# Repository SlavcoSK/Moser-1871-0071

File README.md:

# Moser ChromStyle Pro 1871 – rekonštrukcia PCB a schémy

Reverzné inžinierstvo dosky strihacieho strojčeka **Moser/Wahl 1871-7176**, PCB **E190688**, s mikrokontrolérom **ATtiny461V-10SU**.

## Aktuálne súbory

- [Moser_1871_FINAL_3D_SYNC1.kicad_pcb](Moser_1871_FINAL_3D_SYNC1.kicad_pcb) – aktuálna ručne rekonštruovaná PCB; hlavný zdroj pravdy projektu.
- [Moser_1871_FINAL_3D_SYNC1.kicad_sch](Moser_1871_FINAL_3D_SYNC1.kicad_sch) – schéma odvodená z PCB.

PCB a schéma majú rovnaký základ názvu, aby ich bolo možné zaradiť do jedného projektu KiCad 9. Lokálny projektový súbor `.kicad_pro` je možné vytvoriť alebo ponechať v rovnakom priečinku.

## 3D náhľad dosky

### Predná strana – F.Cu

### Zadná strana – B.Cu

## Zásadné pravidlo rekonštrukcie

Pri rozpore platí toto poradie dôveryhodnosti:

1. meranie a sledovanie spojov na originálnej PCB,
2. čitateľná fotografia originálnej dosky,
3. aktuálny ručne opravený PCB súbor,
4. datasheet jednoznačne identifikovanej súčiastky,
5. staré automatické siete, staré schémy a odhady podľa markingu.

Geometria používateľovej PCB je nadradená. Cesty, zóny, polohy, orientácie ani číslovanie plôšok sa nemajú automaticky meniť. Schéma je rekonštrukcia z PCB, nie autorita nad originálnou doskou.

## Potvrdené tranzistory

| Marking | Typ | Tranzistory | Pinout |
|---|---|---|---|
| FZT968 | FZT968 PNP, SOT-223 | T1, T2 | 1=B, 2=C/tab, 3=E |
| 6CW | BC817-40 NPN, SOT-23 | T4, T5, T6, T13, T15 | 1=B, 2=E, 3=C |
| 1K / 1.K | BC848B NPN, SOT-23 | T3, T11 | 1=B, 2=E, 3=C |
| 3.B | BC856B PNP, SOT-23 | T8, T9, T12, T14 | 1=B, 2=E, 3=C |

Tieto identifikácie sú v KiCad súboroch označené ako **POTVRDENÉ – NEMENIŤ**.

### T7

- marking **HDY0**,
- digitálny tranzistor/BRT potvrdený,
- presný katalógový typ a vnútorné rezistory zatiaľ nepotvrdené,
- aktuálne PCB: T7.1 = N012, T7.2 = GND, T7.3 = N010.

### T10

- marking **P8W** a zvislé číslo **67**,
- digitálny tranzistor/BRT potvrdený,
- presný katalógový typ a vnútorné rezistory zatiaľ nepotvrdené,
- T10.1 = Adapter+,
- T10.2 = BAT+,
- T10.3 = R16.2.

Staré identifikácie T10 ako PMBZ5246B a definitívne tvrdenie PDTC143ET sa nepovažujú za potvrdené.

## Diódy a indikácia

### D1 – ochrana motora

- marking **S4**,
- vpravo je anóda,
- vľavo je katóda,
- aktuálne číslovanie: 1=A, 2=K,
- funkcia ochrannej/flyback diódy motora je potvrdená,
- presný katalógový typ zostáva otvorený; SS24-class je iba pracovný kandidát.

### LED stavu batérie

- D3, D4 a D5 sú zelené LED indikácie nabitia,
- D6 je červená LED nízkeho/vybitého stavu,
- pin 1 = anóda, pin 2 = katóda,
- LED sú ovládané cez katódové vetvy.

Potvrdené väzby:

- D3.2 → R26.1; R26.2 → U1.12,
- D4.2 → R27.1; R27.2 → U1.3,
- D5.2 → R31.2; R31.1 → U1.8,
- D6.2 → R34.1 → R32.1; R32.2 → T14.1.

## Potvrdené merania

- motor: približne **530 mA pri 4 V**,
- akumulátor: **3,6 V / 2000 mAh**, externý test približne **1700 mAh a 6,2 Wh pri 300 mA**,
- automatické vypnutie motora nastalo približne pri **2,885–2,888 V**,
- R37–R40: marking R100, hodnota **0,100 Ω**,
- R41: **0,30 Ω**,
- JP1 a JP2: nulové MELF prepojky, DCR približne **6 mΩ**, indukčnosť pod **0,1 µH**.

## Podpora projektu

Ak vám táto rekonštrukcia pomohla alebo ste jej podklady použili, budeme radi, ak projektu udelíte aspoň **⭐ hviezdičku na GitHube**. Je to jednoduchý spôsob, ako oceniť čas, merania na originálnej PCB a našu spoločnú prácu vloženú do rekonštrukcie.

## Aktuálna pracovná etapa

Dopĺňajú sa kontrolné plôšky **TP**. Každý TP sa najprv vytvorí a pripojí v schéme, následne sa cez aktualizáciu zo schémy prenesie do PCB a umiestni na fyzickú kontrolnú plôšku alebo koniec príslušného prekovu.

Projekt je stále pracovná rekonštrukcia a zatiaľ nie je určený ako výrobný podklad.

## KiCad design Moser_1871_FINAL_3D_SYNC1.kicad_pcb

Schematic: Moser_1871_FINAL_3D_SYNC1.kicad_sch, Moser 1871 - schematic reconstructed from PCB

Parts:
C1, C4: 100 nF (meas. 98 nF)
C2: 100 nF (meas. 97 nF)
C3: 1 nF
C5: 100 nF (meas. 96 nF)
C6: 1 µF (meas. ~0.9 µF)
C8, C10: C1 micro F
C9: C96nF
C11: C97nF
C12: C101nF
D1: S4; ochranna dioda motora; 1=A vpravo, 2=K vlavo;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
D2: Si signal diode; Vf=0.585 V; 1=K, 2=A
D3, D4, D5: ZELENA LED; 1=A, 2=K; riadenie katodou
D6: CERVENA LED LOW BAT; 1=A, 2=K; riadenie katodou
D7: D Si signal diode; Vf=0.585 V; 1=K, 2=A
D10: D
JP1, JP2: 0 ohm MELF; DCR priblizne 6 mOhm; L pod 0.1 uH; P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
P_ADAPTER_NEG1: ADAPTER - independent
P_ADAPTER_POS1: Adapter +
P_BAT_NEG1: BATTERY - independent
P_BAT_POS1: BATTERY + independent
P_MOTOR_NEG1: MOTOR - independent
P_MOTOR_POS1: MOTOR + independent
R1, R10: 10 kΩ
R2: 560 Ω
R3: 33 Ω
R4, R12, R13: 100 Ω
R5: 150 Ω
R6, R7, R8: 1 kΩ
R9: 10 kΩ (measured)
R11: 100 kΩ
R14, R24, R28: R1001
R15, R18, R19, R23, R32, R36: R103
R16, R37, R38, R39, R40: R100
R17: R5603
R20, R21: R5602
R22: R2203
R25: R222
R26, R27, R31, R34: R151
R29: R472
R30: R183
R33: R331
R35: R104
R41: 0.30 ohm; POTVRDENE
SPK1: SPEAKER 3D (existing solder vias retained)
T1, T2: FZT968 PNP; 1=B, 2=C/tab, 3=E; POTVRDENE
T3: BC848B NPN; marking 1K; 1=B, 2=E, 3=C; POTVRDENE
T4, T5, T6, T13, T15: BC817-40 NPN; marking 6CW; 1=B, 2=E, 3=C; POTVRDE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
T7: HDY0; DIGITALNY TRANZISTOR POTVRDENY; PRESNY TYP 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
T8, T9, T12, T14: BC856B PNP; marking 3.B; 1=B, 2=E, 3=C; POTVRDENE
T10: P8W + zvisle 67; DIGITALNY TRANZISTOR POTVRDENY; 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
T11: BC848B NPN; marking 1.K; 1=B, 2=E, 3=C; POTVRDENE
TP1: PCB PAD at 192.000,64.500; original unnumbered
TP2: PCB PAD at 177.500,93.500; original unnumbered
TP3: PCB PAD at 175.500,117.750; original A-
TP4: PCB PAD at 178.500,47.750; original unnumbered
TP5: PCB PAD at 194.500,117.750; original +A
TP6: PCB PAD at 178.500,49.500; original unnumbered
TP7: PCB PAD at 179.500,93.500; original unnumbered
TP8: TestPoint; TestPoint_Pad_D1.0mm
TP9: TestPoint
U1: ATtiny461V-10SU SOIC-20; POTVRDENE

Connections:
Adapter+: C11.2, D7.2 (A), P_ADAPTER_POS1.+A (A), R25.2, R30.2, R33.2, T2.3 (E), T10.1, T15.3, TP5.1
Adapter_Sense: D10.2, R33.1, T15.1
BAT+: P_BAT_POS1.+B (B), R22.1, T2.2 (C), T9.2, T10.2, T12.2, TP1.1
GND: C2.1, C3.1, C3.2, C4.2, C5.1, C5.2, C6.1, C6.2, C8.1, C9.2, C10.1, C11.1, C12.1, D10.1, JP1.1, JP2.1, P_ADAPTER_NEG1.-A (A), P_BAT_NEG1.-B (B), R2.1, R2.2, R4.2, R6.2, R9.2, R11.2, R14.1, R20.2, R29.1, R35.1, R39.2, R40.2, R41.2, T3.2 (E), T4.1 (B), T4.2 (E), T5.2 (E), T6.2 (E), T7.2, T11.2, T13.2, TP2.1, U1.6, U1.7, U1.13, U1.15, U1.16, U1.20
Isense: D1.1 (A), JP1.2, JP2.2, R12.1, R31.1, R37.1, R38.1, R39.1, R40.1, U1.8
MOTOR+: D1.2 (K), P_MOTOR_POS1.+M (M), R8.1, T1.2 (C)
N001: R24.2, T13.1
N002: R25.1, T13.3
N003: R17.1, T9.1
N004: R21.1, T9.3
N005: R22.2
N006: D3.1 (A), D4.1 (A), D5.1 (A), D6.1 (A), T12.3, T14.2, T15.2
N007: D5.2 (K), R31.2
N008: C9.1, R18.1, R20.1, R21.2
N009: R18.2, U1.14
N010: C8.2, R16.1, T7.3
N011: R16.2, T10.3
N012: C10.2, R41.1, T7.1, T8.2
N013: D4.2 (K), R27.1
N014: R27.2, U1.3
N015: D7.1 (K), R24.1, R28.1, U1.17
N016: R23.1, R28.2, T12.1
N017: P_MOTOR_NEG1.-M (M), R11.1, R37.2, R38.2
N018: D6.2 (K), R34.1
N019: R32.1, R34.2, T14.3, U1.1
N020: R15.2, R17.2
N021: R14.2
N022: C12.2, R35.2, R36.1
N023: TP4.1
N024: R29.2, R30.1, T3.1 (B)
N025: R19.1, T11.1
N026: R23.2, T11.3
N027: D3.2 (K), R26.1
N028: R26.2, U1.12
N029: R32.2, T14.1
N030: R15.1, T8.1
N031: R1.1, R19.2, T8.3
N032: TP6.1
N033: R13.1, R36.2, U1.18
N034: C2.2, R8.2, TP7.1, U1.9
N035: R13.2, T6.1 (B)
N036: T6.3 (C)
N037: C1.2, D2.1 (K), T3.3 (C)
N038: D2.2 (A), R4.1
N039: R3.1, T4.3 (C)
N040: R3.2, T1.1 (B)
N041: C4.1, R10.2, U1.5
N042: R1.2, R9.1, U1.11
N043: T1.3 (E)
N044: C1.1, R10.1, U1.10
N045: R7.1, U1.2
N046: R6.1, U1.4
N047: R12.2, U1.19
N048: R5.1, T5.3 (C)
N049: R7.2, T5.1 (B)
N050: R5.2, T2.1 (B)
N051: TP3.1

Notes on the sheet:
T7: marking HDY0; exact type unconfirmed. Pin numbering follows the attached PCB revision (5).
SPK1 is 3D-only in the PCB and therefore has no electrical pins in this draft.
T10: pin 1=Adapter+, pin 2=BAT+, pin 3=R16.2 network. Marking P8W + vertical 67; exact type unconfirmed.
MOSER 1871 - COMPLETE CONNECTIVITY DRAFT EXTRACTED FROM PCB
Adapter_Sense is the physical island R33.1-D10.2-T15.1. Verify against the original board before manufacturing.

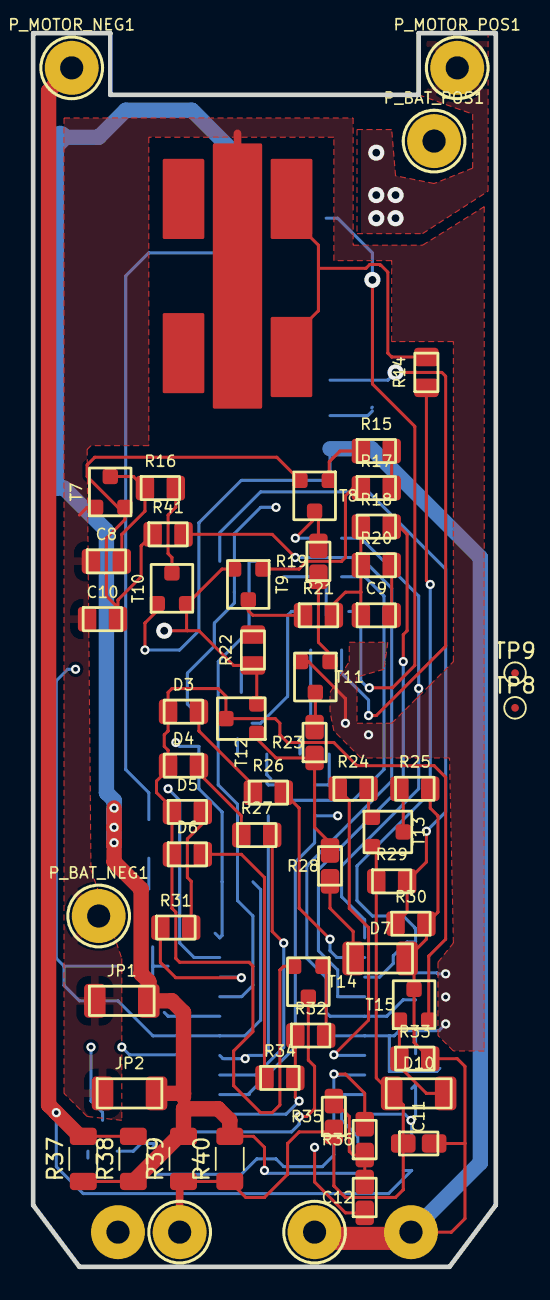
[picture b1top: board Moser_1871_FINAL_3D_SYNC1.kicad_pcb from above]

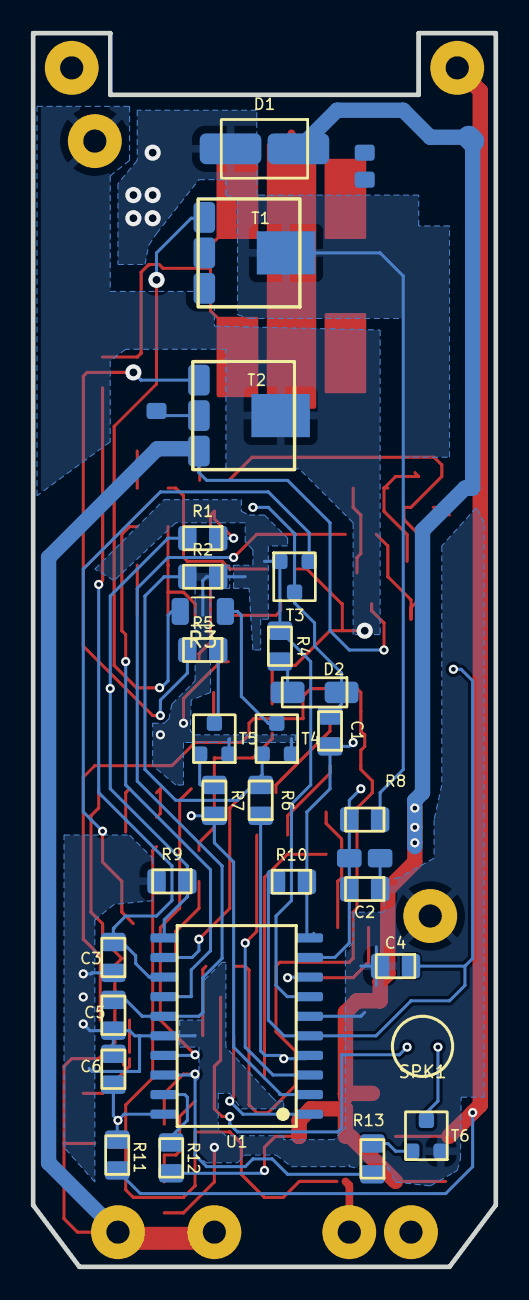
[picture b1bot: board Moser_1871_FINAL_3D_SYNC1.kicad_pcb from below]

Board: 2 copper layers, 30.0 x 80.0 mm, 94 parts (29 on the bottom side), 50 nets.

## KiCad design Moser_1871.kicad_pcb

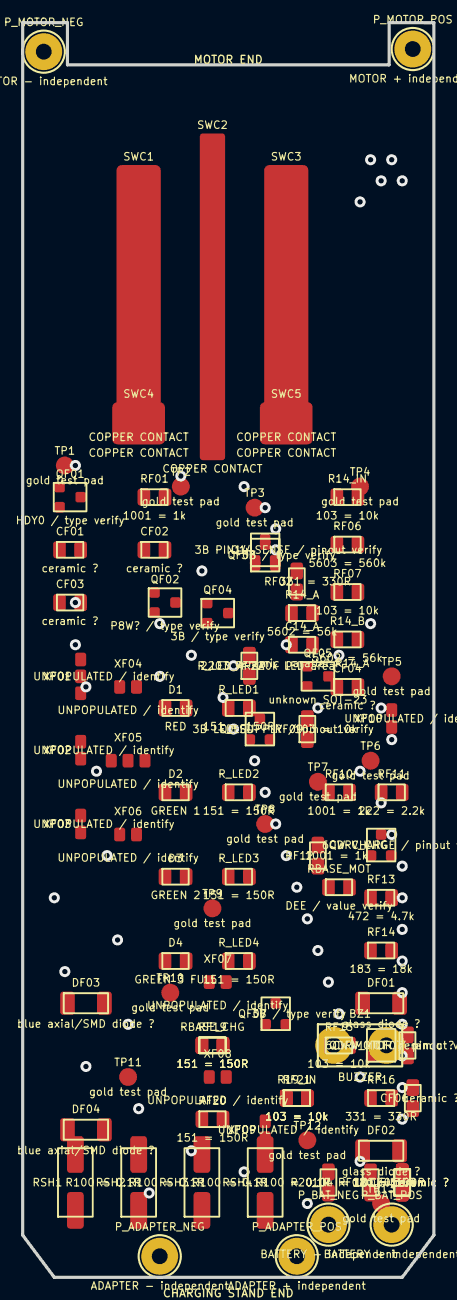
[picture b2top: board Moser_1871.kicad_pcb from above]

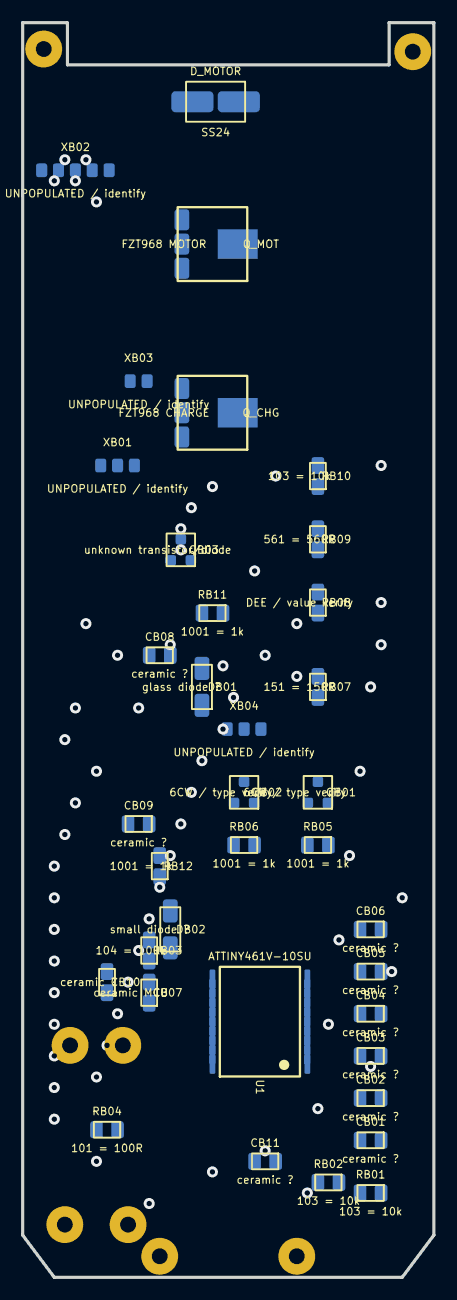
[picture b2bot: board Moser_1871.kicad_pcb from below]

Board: 2 copper layers, 39.0 x 119.0 mm, 130 parts (36 on the bottom side), 20 nets, no tracks yet.

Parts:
BZ1: BUZZER; TH_2P
C14_A: ceramic parallel R14_A; 0805_2P
C20_FILTER: ceramic ?; 0805_2P
CB01, CB02, CB03, CB04, CB05, CB06, CB08, CB09, CB10, CB11: ceramic ?; 0805_2P
CB07: ceramic MCU; 0805_2P
CF01, CF02, CF03, CF04, CF05, CF06, CF07: ceramic ?; 0805_2P
D1: RED; 0805_2P
D2: GREEN 1; 0805_2P
D3: GREEN 2; 0805_2P
D4: GREEN 3 FULL; 0805_2P
DB01: glass diode ?; MELF_2P
DB02: small diode ?; MELF_2P
DF01, DF02: glass diode ?; MELF_2P
DF03, DF04: blue axial/SMD diode ?; MELF_2P
D_MOTOR: SS24; SMB_2P
P_ADAPTER_NEG: ADAPTER - independent; TH_SINGLE_PAD
P_ADAPTER_POS: ADAPTER + independent; TH_SINGLE_PAD
P_BAT_NEG: BATTERY - independent; TH_SINGLE_PAD
P_BAT_POS: BATTERY + independent; TH_SINGLE_PAD
P_MOTOR_NEG: MOTOR - independent; TH_SINGLE_PAD
P_MOTOR_POS: MOTOR + independent; TH_SINGLE_PAD
Q14: 3B PIN14 SENSE / pinout verify; SOT-23
QB01, QB02: 6CW / type verify; SOT-23
QB03: unknown transistor/diode; SOT-23
QDRV_CHG: 6CW CHARGE / pinout verify; SOT-23
QDRV_MOT: 6CW MOTOR / pinout verify; SOT-23
QF01: HDY0 / type verify; SOT-23
QF02: P8W? / type verify; SOT-23
QF03, QF04, QF07: 3B / type verify; SOT-23
QF05: unknown SOT-23; SOT-23
Q_CHG: FZT968 CHARGE; SOT-223
Q_LED: 3B LED SUPPLY / pinout verify; SOT-23
Q_MOT: FZT968 MOTOR; SOT-223
R14_A, R14_B: 5602 = 56k; 0805_2P
R14_IN, R19_IN: 103 = 10k; 0805_2P
R20_IN: 104 = 100k; 0805_2P
RB01, RB02, RB10: 103 = 10k; 0805_2P
RB03: 104 = 100k; 0805_2P
RB04: 101 = 100R; 0805_2P
RB05, RB06, RB11, RB12: 1001 = 1k; 0805_2P
RB07: 151 = 150R; 0805_2P
RB08: DEE / value verify; 0805_2P
RB09: 561 = 560R; 0805_2P
RBASE_CHG: 151 = 150R; 0805_2P
RBASE_MOT: DEE / value verify; 0805_2P
RF01, RF10, RF12: 1001 = 1k; 0805_2P
RF02, RF16: 331 = 330R; 0805_2P
RF06: 5603 = 560k; 0805_2P
RF07, RF09, RF15, RF21: 103 = 10k; 0805_2P
RF11: 222 = 2.2k; 0805_2P
RF13: 472 = 4.7k; 0805_2P
RF14: 183 = 18k; 0805_2P
RF18: 101 = 100R; 0805_2P
RF19, RF20: 151 = 150R; 0805_2P
RSH1, RSH2, RSH3, RSH4: R100 = 0.1R; 2512_2P
R_LED1, R_LED2, R_LED3, R_LED4: 151 = 150R; 0805_2P
R_LED_AREA: 2203 = 220k LED area; 0805_2P
SWC1, SWC2, SWC3, SWC4, SWC5: COPPER CONTACT; SWITCH_CONTACT
TP1, TP2, TP3, TP4, TP5, TP6, TP7, TP8, TP9, TP10, TP11, TP12, TP13: gold test pad; TEST_PAD
U1: ATTINY461V-10SU; SOIC-20
XB01, XB04: UNPOPULATED / identify; UNIDENTIFIED_3P
XB02: UNPOPULATED / identify; UNIDENTIFIED_5P
XB03: UNPOPULATED / identify; UNIDENTIFIED_2P
XF01, XF05: UNPOPULATED / identify; UNIDENTIFIED_3P
XF02, XF03, XF04, XF06, XF07, XF08, XF09, XF10: UNPOPULATED / identify; UNIDENTIFIED_2P

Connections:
ADAPTER+: P_ADAPTER_POS.1, Q_CHG.3
BAT+: P_BAT_POS.1, Q_CHG.2, Q_CHG.4, Q_MOT.3, U1.5, U1.15
GND: C20_FILTER.2, U1.6, U1.16
LED_COMMON: D1.2, D2.2, D3.2, D4.2
MOTOR+: D_MOTOR.2, P_MOTOR_POS.1, Q_MOT.2, Q_MOT.4
MOTOR-: D_MOTOR.1, P_MOTOR_NEG.1
PIN14_N1: C14_A.1, R14_A.1, R14_IN.2
PIN14_N2: C14_A.2, R14_A.2, R14_B.1
PIN14_QC: Q14.3, R14_B.2
Q_CHG_BASE: Q_CHG.1, RBASE_CHG.2
Q_MOT_BASE: Q_MOT.1, RBASE_MOT.2
SHUNT12_B: R19_IN.1, RSH1.2, RSH2.2
SHUNT34_B: R20_IN.1, RSH3.2, RSH4.2
U1_PIN1_PB0: D4.1, R_LED4.1, U1.1
U1_PIN3_PB2: D2.1, R_LED2.1, U1.3
U1_PIN8_PB5: D3.1, R_LED3.1, U1.8
U1_PIN12_PA6: D1.1, R_LED1.1, U1.12
U1_PIN14_ADC3: R14_IN.1, U1.14
U1_PIN19_ADC1: R19_IN.2, U1.19
U1_PIN20_ADC0: C20_FILTER.1, R20_IN.2, U1.20

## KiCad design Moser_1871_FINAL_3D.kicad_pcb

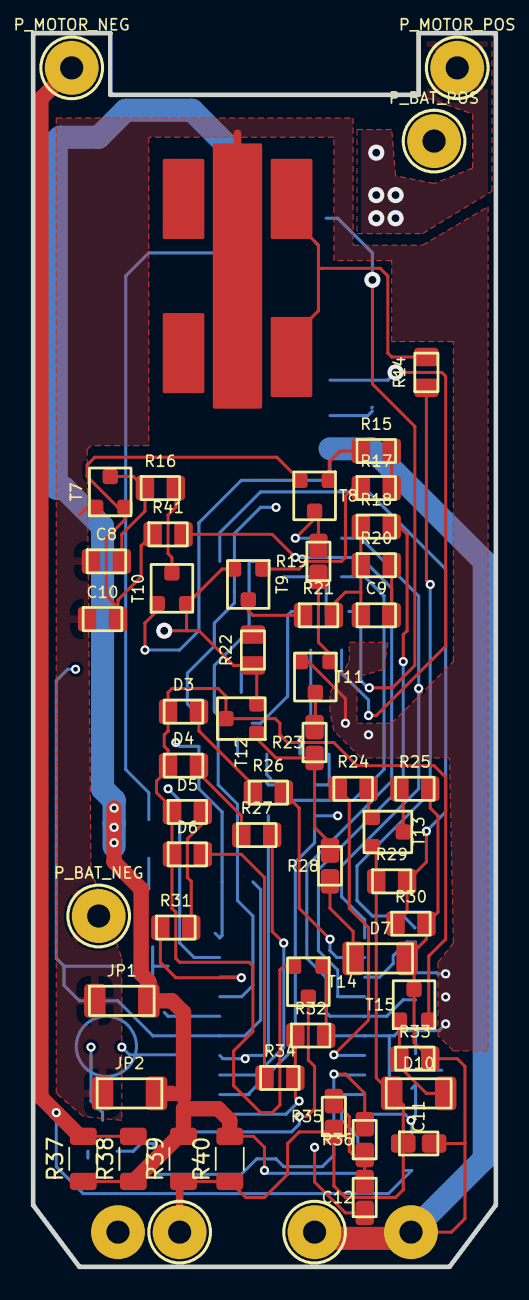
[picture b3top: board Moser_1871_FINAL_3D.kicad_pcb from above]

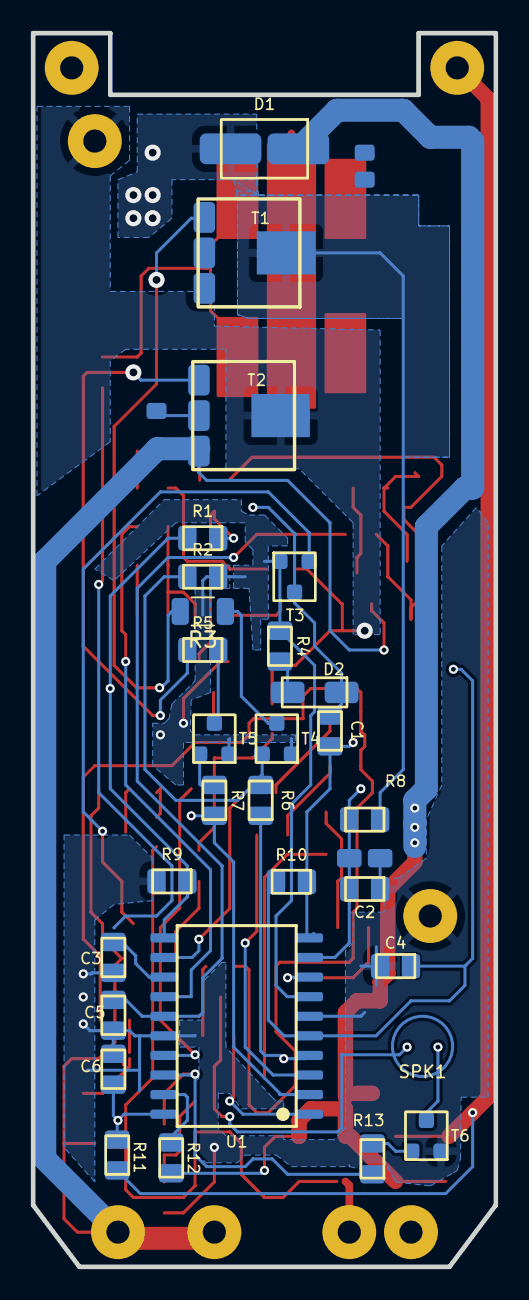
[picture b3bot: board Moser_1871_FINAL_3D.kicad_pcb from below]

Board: 2 copper layers, 30.0 x 80.0 mm, 85 parts (29 on the bottom side), 5 nets.

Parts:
C1, C4: 100 nF (meas. 98 nF); 0805_2P
C2: 100 nF (meas. 97 nF); 0805_2P
C3: 1 nF; 0805_2P
C5: 100 nF (meas. 96 nF); 0805_2P
C6: 1 µF (meas. ~0.9 µF); 0805_2P
C8, C10: C1 micro F; 0805_2P
C9: C96nF; 0805_2P
C11: C97nF; 0805_2P
C12: C101nF; 0805_2P
D1: S4; SMB_2P
D2: Si signal diode; Vf=0.585 V; 1=K, 2=A; MELF_2P
D3, D4, D5, D6: D; 0805_2P
D7: D Si signal diode; Vf=0.585 V; 1=K, 2=A; MELF_2P
D10: D; MELF_2P
JP1, JP2: MELF jumper DCR ≈ 6 mΩ; MELF_2P
P_ADAPTER_NEG: ADAPTER - independent; TH_SINGLE_PAD
P_ADAPTER_POS: Adapter +; TH_SINGLE_PAD
P_BAT_NEG: BATTERY - independent; TH_SINGLE_PAD
P_BAT_POS: BATTERY + independent; TH_SINGLE_PAD
P_MOTOR_NEG: MOTOR - independent; TH_SINGLE_PAD
P_MOTOR_POS: MOTOR + independent; TH_SINGLE_PAD
R1, R10: 10 kΩ; 0805_2P
R2: 560 Ω; 0805_2P
R3: 33 Ω; R_1206_3216Metric
R4, R12, R13: 100 Ω; 0805_2P
R5: 150 Ω; 0805_2P
R6, R7, R8: 1 kΩ; 0805_2P
R9: 10 kΩ (measured); 0805_2P
R11: 100 kΩ; 0805_2P
R14, R24, R28: R1001; 0805_2P
R15, R18, R19, R23, R32, R36: R103; 0805_2P
R16: R100; 0805_2P
R17: R5603; 0805_2P
R20, R21: R5602; 0805_2P
R22: R2203; 0805_2P
R25: R222; 0805_2P
R26, R27, R31, R34: R151; 0805_2P
R29: R472; 0805_2P
R30: R183; 0805_2P
R33: R331; 0805_2P
R35: R104; 0805_2P
R37, R38, R39, R40: R100; R_1206_3216Metric
R41: R0,30 ohm; 0805_2P
SPK1: SPEAKER 3D (existing solder vias retained); SPK_3D_ONLY
T1, T2: FZT968 PNP; 1=B, 2=C/tab, 3=E; SOT-223
T3: BC848B (marking 1K); 1=B, 2=E, 3=C; SOT-23
T4, T5, T6: BC817-40 (marking 6CW); 1=B, 2=E, 3=C; SOT-23
T7: Digital PNP BRT (DTA114E-type), marking HDY0; PCB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; SOT-23
T8, T9, T12, T14: 3B; SOT-23
T10: P8W; SOT-23
T11: 1.K; SOT-23
T13, T15: 6CW; SOT-23
U1: ATtiny461V-10SU SOIC-20; SOIC-20_7.5x12.8mm_P1.27mm

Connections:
Adapter+: C11.2, P_ADAPTER_POS.+A, R33.2, T2.3, T10.1, T15.3
Adapter-: P_ADAPTER_NEG.-A, R39.2, R40.2
BAT+: P_BAT_POS.+B, R22.1, T2.2, T9.2, T10.2
GND: C2.1, C3.1, C3.2, C4.2, C5.2, C6.1, C8.1, C9.2, C10.1, C11.1, C12.1, JP1.1, JP2.1, P_BAT_NEG.-B, R2.1, R9.2, R14.1, T3.2, T4.2, T5.2, T6.2, T7.2, T11.2, U1.6, U1.16
MOTOR+: D1.2, P_MOTOR_POS.+M, T1.2
